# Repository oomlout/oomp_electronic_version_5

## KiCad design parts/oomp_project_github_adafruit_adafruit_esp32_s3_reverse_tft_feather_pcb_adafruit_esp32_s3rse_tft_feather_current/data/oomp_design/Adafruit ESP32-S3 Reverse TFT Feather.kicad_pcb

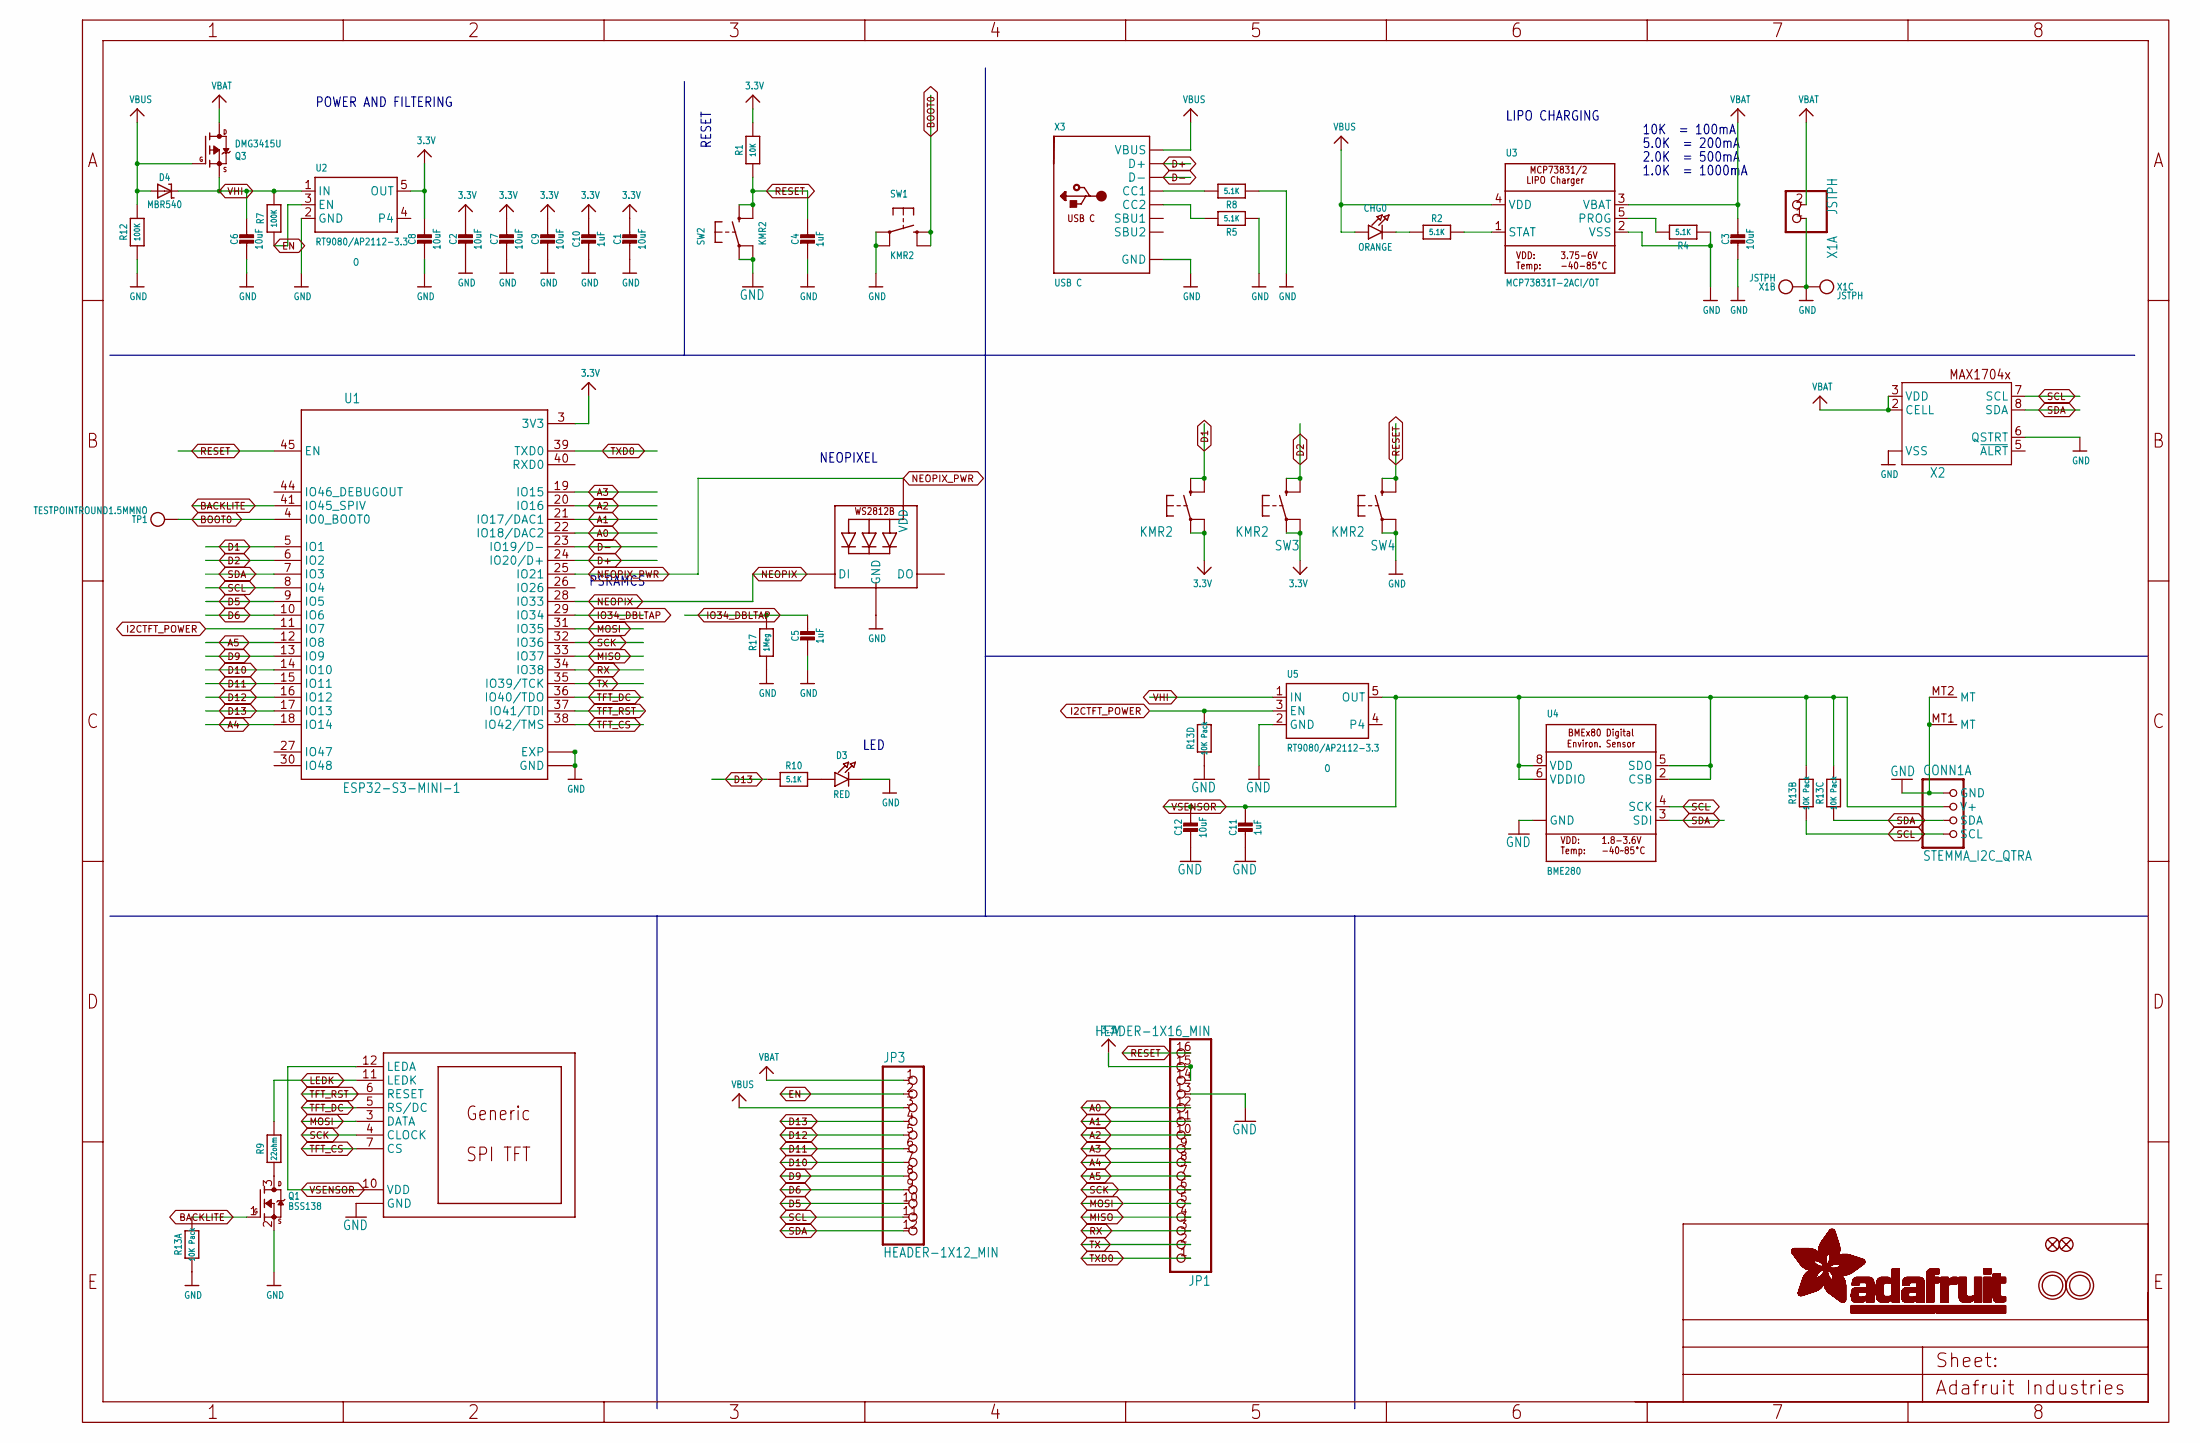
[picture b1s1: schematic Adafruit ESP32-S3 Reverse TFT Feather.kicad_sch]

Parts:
C1, C2, C3, C6, C7, C8, C9, C12: 10uF; 0805-NO
C4, C5, C10, C11: 1uF; 0603-NO
CHG0: ORANGE; CHIPLED_0603_NOOUTLINE
CONN1: STEMMA_I2C_QTRA; JST_SH4_RA; LCSC C145961
D3: RED; CHIPLED_0603_NOOUTLINE
D4: MBR540; SOD-123
DISP1: DISP_LCD_GENERIC_SPI_1.14IN_240X135_WRAPUNDER; TFT_1.14IN_240X135_WRAPUNDER
JP1: HEADER-1X16_MIN; 1X16_ROUND_MIN
JP3: HEADER-1X12_MIN; 1X12_ROUND_MIN
LED1: WS2812B_SK6805_1515; SK6805_1515; LCSC C2890035
Q1: BSS138; SC70
Q3: DMG3415U; SOT23-R
R1: 10K; 0603-NO
R2, R4, R5, R8, R10: 5.1K; 0603-NO
R7, R12: 100K; 0603-NO
R9: 22ohm; 0603-NO
R13: 10K Pack; RESPACK_4X0603
R17: 1Meg; 0603-NO
SW1, SW2, SW3, SW4, SW5: KMR2; BTN_RKB2_4.6X2.8
TP1: TESTPOINTROUND1.5MMNO; TESTPOINT_ROUND_1.5MM_NO
U1: ESP32-S3-MINI-1; ESP32-S2-MINI-1; MANUFACTURER_PART_NUMBER ESP32-S2-MINI-1
U2, U5: RT9080/AP2112-3.3; SOT23-5; JLC_ROTATION 0
U3: MCP73831T-2ACI/OT; SOT23-5; JLC_ROTATION 270
U4: BME280
U$31, U$32: MOUNTINGHOLE2.5; MOUNTINGHOLE_2.5_PLATED
U$34, U$35: FIDUCIAL_1MM
X1: JSTPH; JSTPH2_BATT; LCSC C47647
X2: MAX17048/T; TDFN8_2X2MM
X3: USB C; USB_C_CUSB31-CFM2AX-01-X; LCSC C165948

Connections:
3.3V: C1.1, C2.1, C7.1, C8.1, C9.1, C10.1, JP1.14, JP1.15, R1.2, SW3.A, SW3.A' (P1), SW5.A, SW5.A' (P1), U1.3 (3V3), U2.5 (OUT)
A0: JP1.12, U1.22 (IO18/DAC2)
A1: JP1.11, U1.21 (IO17/DAC1)
A2: JP1.10, U1.20 (IO16)
A3: JP1.9, U1.19 (IO15)
A4: JP1.8, U1.18 (IO14)
A5: JP1.7, U1.12 (IO8)
BACKLITE: Q1.1 (G), R13.8 (2), U1.41 (IO45_SPIV)
BOOT0: SW1.B (S), SW1.B' (S1), TP1.P$1, U1.4 (IO0_BOOT0)
D1: SW5.B (S), SW5.B' (S1), U1.5 (IO1)
D2: SW3.B (S), SW3.B' (S1), U1.6 (IO2)
D5: JP3.10, U1.9 (IO5)
D6: JP3.9, U1.10 (IO6)
D9: JP3.8, U1.13 (IO9)
D10: JP3.7, U1.14 (IO10)
D11: JP3.6, U1.15 (IO11)
D12: JP3.5, U1.16 (IO12)
D13: JP3.4, R10.1, U1.17 (IO13)
D+: U1.24 (IO20/D+), X3.A6 (D+), X3.B6 (D+)
D-: U1.23 (IO19/D-), X3.A7 (D-), X3.B7 (D-)
EN: JP3.2, R7.1, U2.3 (EN)
GND: C1.2, C2.2, C3.2, C4.2, C5.2, C6.2, C7.2, C8.2, C9.2, C10.2, C11.2, C12.2, CONN1.1 (GND), CONN1.MT1 (MT), CONN1.MT2 (MT), D3.C, DISP1.8 (GND), DISP1.13 (GND), JP1.13, LED1.4 (GND), Q1.2 (S), R4.1, R5.1, R8.1, R12.1, R13.1, R13.4 (1), R17.1, SW1.A, SW1.A' (P1), SW2.A, SW2.A' (P1), SW4.A, SW4.A' (P1), U1.1 (GND), U1.2 (GND), U1.42 (GND), U1.43 (GND), U1.46 (GND), U1.47 (GND), U1.48 (GND), U1.49 (GND), U1.50 (GND), U1.51 (GND), U1.52 (GND), U1.53 (GND), U1.54 (GND), U1.55 (GND), U1.56 (GND), U1.57 (GND), U1.58 (GND), U1.59 (GND), U1.60 (GND), U1.61 (EXP), U1.62 (GND), U1.63 (GND), U1.64 (GND), U1.65 (GND), U1.66 (EXP), U1.67 (EXP), U1.68 (EXP), U1.69 (EXP), U1.70 (EXP), U1.71 (EXP), U1.72 (EXP), U1.73 (EXP), U2.2 (GND), U3.2 (VSS), U4.1 (GND), U4.7 (GND), U5.2 (GND), X1.1, X1.NC1, X1.NC2, X2.1 (VSS), X2.4 (VSS), X2.6 (QSTRT), X2.THERMAL (VSS), X3.A1B12 (GND), X3.B1A12 (GND)
I2CTFT_POWER: R13.5 (2), U1.11 (IO7), U5.3 (EN)
IO34_DBLTAP: C5.1, R17.2, U1.29 (IO34)
LEDK: DISP1.11 (LEDK), R9.2
MISO: JP1.4, U1.33 (IO37)
MOSI: DISP1.3 (DATA), JP1.5, U1.31 (IO35)
unnamed: CHG0.C, R2.1
unnamed: Q1.3 (D), R9.1
unnamed: R2.2, U3.1 (STAT)
unnamed: R4.2, U3.5 (PROG)
unnamed: D3.A, R10.2
unnamed: R8.2, X3.A5 (CC1)
unnamed: R5.2, X3.B5 (CC2)
NEOPIX: LED1.1 (DI), U1.28 (IO33)
NEOPIX_PWR: LED1.2 (VDD), U1.25 (IO21)
RESET: C4.1, JP1.16, R1.1, SW2.B (S), SW2.B' (S1), SW4.B (S), SW4.B' (S1), U1.45 (EN)
RX: JP1.3, U1.34 (IO38)
SCK: DISP1.4 (CLOCK), JP1.6, U1.32 (IO36)
SCL: CONN1.4 (SCL), JP3.11, R13.2 (1), U1.8 (IO4), U4.4 (SCK), X2.7 (SCL)
SDA: CONN1.3 (SDA), JP3.12, R13.3 (1), U1.7 (IO3), U4.3 (SDI), X2.8 (SDA)
TFT_CS: DISP1.7 (CS), U1.38 (IO42/TMS)
TFT_DC: DISP1.5 (RS/DC), U1.36 (IO40/TDO)
TFT_RST: DISP1.6 (RESET), U1.37 (IO41/TDI)
TX: JP1.2, U1.35 (IO39/TCK)
TXD0: JP1.1, U1.39 (TXD0)
VBAT: C3.1, JP3.1, Q3.3 (D), U3.3 (VBAT), X1.2, X2.2 (CELL), X2.3 (VDD)
VBUS: CHG0.A, D4.A, JP3.3, Q3.1 (G), R12.2, U3.4 (VDD), X3.A4B9 (VBUS), X3.B4A9 (VBUS)
VHI: C6.1, D4.C, Q3.2 (S), R7.2, U2.1 (IN), U5.1 (IN)
VSENSOR: C11.1, C12.1, CONN1.2 (V+), DISP1.10 (VDD), DISP1.12 (LEDA), R13.6 (2), R13.7 (2), U4.2 (CSB), U4.5 (SDO), U4.6 (VDDIO), U4.8 (VDD), U5.5 (OUT)

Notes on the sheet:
LED
5.0K = 200mA
POWER AND FILTERING
10K = 100mA
LIPO CHARGING
NEOPIXEL
RESET
1.0K = 1000mA
PSRAMCS
2.0K = 500mA

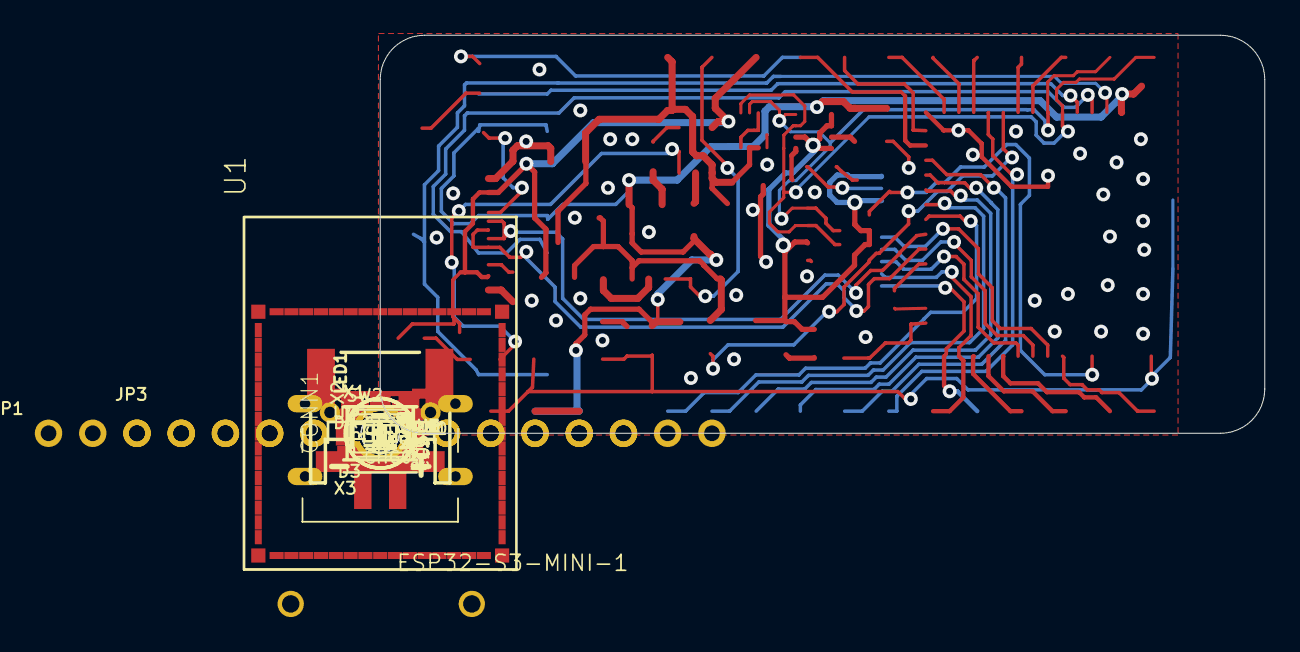
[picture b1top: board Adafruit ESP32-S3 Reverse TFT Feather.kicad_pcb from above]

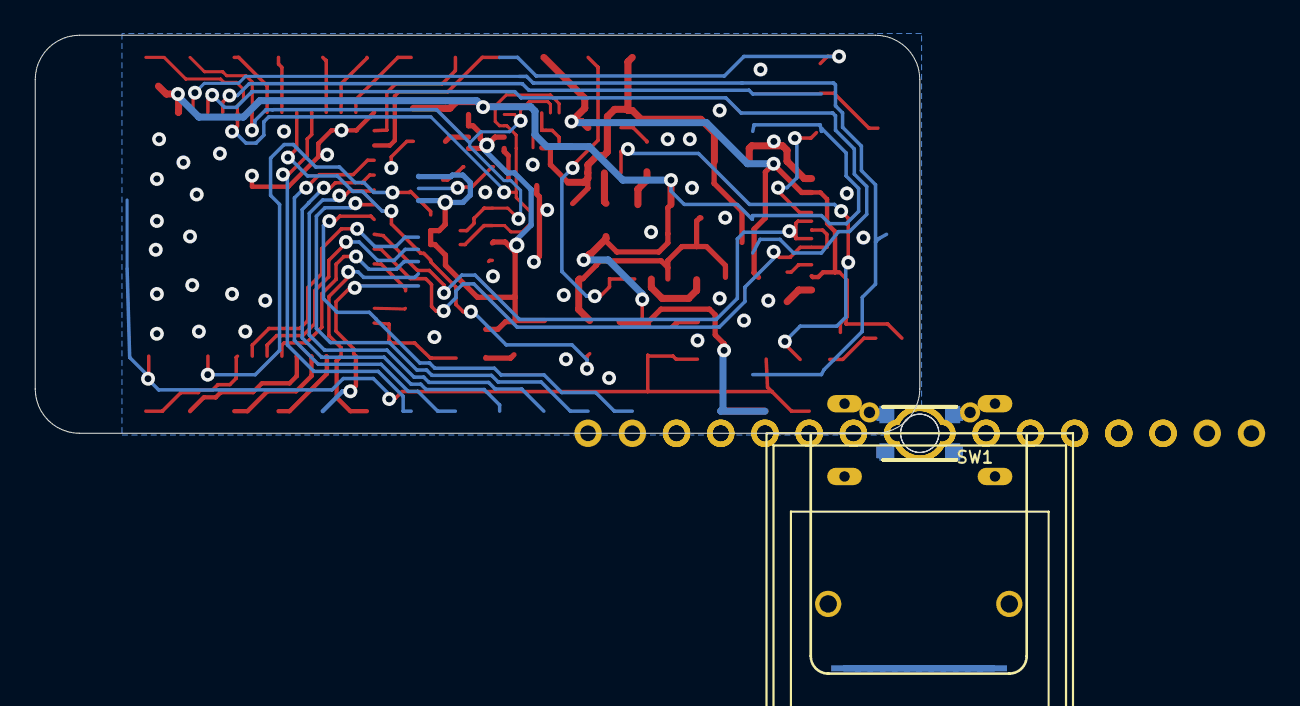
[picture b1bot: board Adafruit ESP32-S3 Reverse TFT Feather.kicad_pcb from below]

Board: 2 copper layers, 50.8 x 22.9 mm, 90 parts (11 on the bottom side), 50 nets.

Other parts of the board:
PLABEL0: PLABEL0
PLABEL1: PLABEL1
PLABEL2: PLABEL2
PLABEL3: PLABEL3
PLABEL4: PLABEL4
PLABEL5: PLABEL5
PLABEL6: PLABEL6
PLABEL7: PLABEL7
PLABEL8: PLABEL8
PLABEL9: PLABEL9
PLABEL10: PLABEL10
PLABEL11: PLABEL11
PLABEL12: PLABEL12
PLABEL13: PLABEL13
PLABEL14: PLABEL14
PLABEL15: PLABEL15
PLABEL16: PLABEL16
PLABEL17: PLABEL17
PLABEL18: PLABEL18
PLABEL19: PLABEL19
PLABEL20: PLABEL20
PLABEL21: PLABEL21
PLABEL22: PLABEL22
PLABEL23: PLABEL23
PLABEL24: PLABEL24
PLABEL25: PLABEL25
PLABEL26: PLABEL26
PLABEL27: PLABEL27
PLABEL28: PLABEL28
PLABEL29: PLABEL29
PLABEL30: PLABEL30
PLABEL31: PLABEL31
PLABEL33: PLABEL33
PLABEL34: PLABEL34
PLABEL35: PLABEL35
PLABEL36: PLABEL36
PLABEL37: PLABEL37
UNK_HOLE_0: dummyfp0
UNK_HOLE_1: dummyfp1

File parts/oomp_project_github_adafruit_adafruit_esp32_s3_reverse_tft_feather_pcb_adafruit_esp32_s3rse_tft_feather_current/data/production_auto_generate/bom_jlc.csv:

Comment,Designator,Footprint,LCSC Part #
,JP3,Adafruit ESP32-S3 Reverse TFT Feather-import-fps:1X12_ROUND_MIN,C7501588
,JP1,Adafruit ESP32-S3 Reverse TFT Feather-import-fps:1X16_ROUND_MIN,C7501270
,PLABEL0,Adafruit ESP32-S3 Reverse TFT Feather-import-fps:PLABEL0,
,PLABEL1,Adafruit ESP32-S3 Reverse TFT Feather-import-fps:PLABEL1,
,PLABEL10,Adafruit ESP32-S3 Reverse TFT Feather-import-fps:PLABEL10,
,PLABEL11,Adafruit ESP32-S3 Reverse TFT Feather-import-fps:PLABEL11,
,PLABEL12,Adafruit ESP32-S3 Reverse TFT Feather-import-fps:PLABEL12,
,PLABEL13,Adafruit ESP32-S3 Reverse TFT Feather-import-fps:PLABEL13,
,PLABEL14,Adafruit ESP32-S3 Reverse TFT Feather-import-fps:PLABEL14,
,PLABEL15,Adafruit ESP32-S3 Reverse TFT Feather-import-fps:PLABEL15,
,PLABEL16,Adafruit ESP32-S3 Reverse TFT Feather-import-fps:PLABEL16,
,PLABEL17,Adafruit ESP32-S3 Reverse TFT Feather-import-fps:PLABEL17,
,PLABEL18,Adafruit ESP32-S3 Reverse TFT Feather-import-fps:PLABEL18,
,PLABEL19,Adafruit ESP32-S3 Reverse TFT Feather-import-fps:PLABEL19,
,PLABEL2,Adafruit ESP32-S3 Reverse TFT Feather-import-fps:PLABEL2,
,PLABEL20,Adafruit ESP32-S3 Reverse TFT Feather-import-fps:PLABEL20,
,PLABEL21,Adafruit ESP32-S3 Reverse TFT Feather-import-fps:PLABEL21,
,PLABEL22,Adafruit ESP32-S3 Reverse TFT Feather-import-fps:PLABEL22,
,PLABEL23,Adafruit ESP32-S3 Reverse TFT Feather-import-fps:PLABEL23,
,PLABEL24,Adafruit ESP32-S3 Reverse TFT Feather-import-fps:PLABEL24,
,PLABEL25,Adafruit ESP32-S3 Reverse TFT Feather-import-fps:PLABEL25,
,PLABEL26,Adafruit ESP32-S3 Reverse TFT Feather-import-fps:PLABEL26,
,PLABEL27,Adafruit ESP32-S3 Reverse TFT Feather-import-fps:PLABEL27,
,PLABEL28,Adafruit ESP32-S3 Reverse TFT Feather-import-fps:PLABEL28,
,PLABEL29,Adafruit ESP32-S3 Reverse TFT Feather-import-fps:PLABEL29,
,PLABEL3,Adafruit ESP32-S3 Reverse TFT Feather-import-fps:PLABEL3,
,PLABEL30,Adafruit ESP32-S3 Reverse TFT Feather-import-fps:PLABEL30,
,PLABEL31,Adafruit ESP32-S3 Reverse TFT Feather-import-fps:PLABEL31,
,PLABEL33,Adafruit ESP32-S3 Reverse TFT Feather-import-fps:PLABEL33,
,PLABEL34,Adafruit ESP32-S3 Reverse TFT Feather-import-fps:PLABEL34,
,PLABEL35,Adafruit ESP32-S3 Reverse TFT Feather-import-fps:PLABEL35,
,PLABEL36,Adafruit ESP32-S3 Reverse TFT Feather-import-fps:PLABEL36,
,PLABEL37,Adafruit ESP32-S3 Reverse TFT Feather-import-fps:PLABEL37,
,PLABEL4,Adafruit ESP32-S3 Reverse TFT Feather-import-fps:PLABEL4,
,PLABEL5,Adafruit ESP32-S3 Reverse TFT Feather-import-fps:PLABEL5,
,PLABEL6,Adafruit ESP32-S3 Reverse TFT Feather-import-fps:PLABEL6,
,PLABEL7,Adafruit ESP32-S3 Reverse TFT Feather-import-fps:PLABEL7,
,PLABEL8,Adafruit ESP32-S3 Reverse TFT Feather-import-fps:PLABEL8,
,PLABEL9,Adafruit ESP32-S3 Reverse TFT Feather-import-fps:PLABEL9,
,TP1,Adafruit ESP32-S3 Reverse TFT Feather-import-fps:TESTPOINT_ROUND_1.5MM_NO,
100K,"R7,R12",Adafruit ESP32-S3 Reverse TFT Feather-import-fps:0603-NO,C25803
10K,R1,Adafruit ESP32-S3 Reverse TFT Feather-import-fps:0603-NO,C98220
10K Pack,R13,Adafruit ESP32-S3 Reverse TFT Feather-import-fps:RESPACK_4X0603,C98220
10uF,"C1,C2,C3,C6,C7,C8,C9,C12",Adafruit ESP32-S3 Reverse TFT Feather-import-fps:0805-NO,
1Meg,R17,Adafruit ESP32-S3 Reverse TFT Feather-import-fps:0603-NO,C2907003
1uF,"C4,C5,C10,C11",Adafruit ESP32-S3 Reverse TFT Feather-import-fps:0603-NO,C5673
22ohm,R9,Adafruit ESP32-S3 Reverse TFT Feather-import-fps:0603-NO,C23345
5.1K,"R2,R4,R5,R8,R10",Adafruit ESP32-S3 Reverse TFT Feather-import-fps:0603-NO,C23186
BME280,U4,Adafruit ESP32-S3 Reverse TFT Feather-import-fps:BME280,
BSS138,Q1,Adafruit ESP32-S3 Reverse TFT Feather-import-fps:SC70,C52895
DISP_LCD_GENERIC_SPI_1.14IN_240X135_WRAPUNDER,DISP1,Adafruit ESP32-S3 Reverse TFT Feather-import-fps:TFT_1.14IN_240X135_WRAPUNDER,
DMG3415U,Q3,Adafruit ESP32-S3 Reverse TFT Feather-import-fps:SOT23-R,
ESP32-S3-MINI-1,U1,Adafruit ESP32-S3 Reverse TFT Feather-import-fps:ESP32-S2-MINI-1,
FIDUCIAL_1MM,"U$34,U$35",Adafruit ESP32-S3 Reverse TFT Feather-import-fps:FIDUCIAL_1MM,
JSTPH,X1,Adafruit ESP32-S3 Reverse TFT Feather-import-fps:JSTPH2_BATT,
KMR2,"SW1,SW2,SW3,SW4,SW5",Adafruit ESP32-S3 Reverse TFT Feather-import-fps:BTN_RKB2_4.6X2.8,
MAX17048/T,X2,Adafruit ESP32-S3 Reverse TFT Feather-import-fps:TDFN8_2X2MM,
MBR540,D4,Adafruit ESP32-S3 Reverse TFT Feather-import-fps:SOD-123,
MCP73831T-2ACI/OT,U3,Adafruit ESP32-S3 Reverse TFT Feather-import-fps:SOT23-5,
ORANGE,CHG0,Adafruit ESP32-S3 Reverse TFT Feather-import-fps:CHIPLED_0603_NOOUTLINE,
RED,D3,Adafruit ESP32-S3 Reverse TFT Feather-import-fps:CHIPLED_0603_NOOUTLINE,
RT9080/AP2112-3.3,"U2,U5",Adafruit ESP32-S3 Reverse TFT Feather-import-fps:SOT23-5,
STEMMA_I2C_QTRA,CONN1,Adafruit ESP32-S3 Reverse TFT Feather-import-fps:JST_SH4_RA,
USB C,X3,Adafruit ESP32-S3 Reverse TFT Feather-import-fps:USB_C_CUSB31-CFM2AX-01-X,
WS2812B_SK6805_1515,LED1,Adafruit ESP32-S3 Reverse TFT Feather-import-fps:SK6805_1515,

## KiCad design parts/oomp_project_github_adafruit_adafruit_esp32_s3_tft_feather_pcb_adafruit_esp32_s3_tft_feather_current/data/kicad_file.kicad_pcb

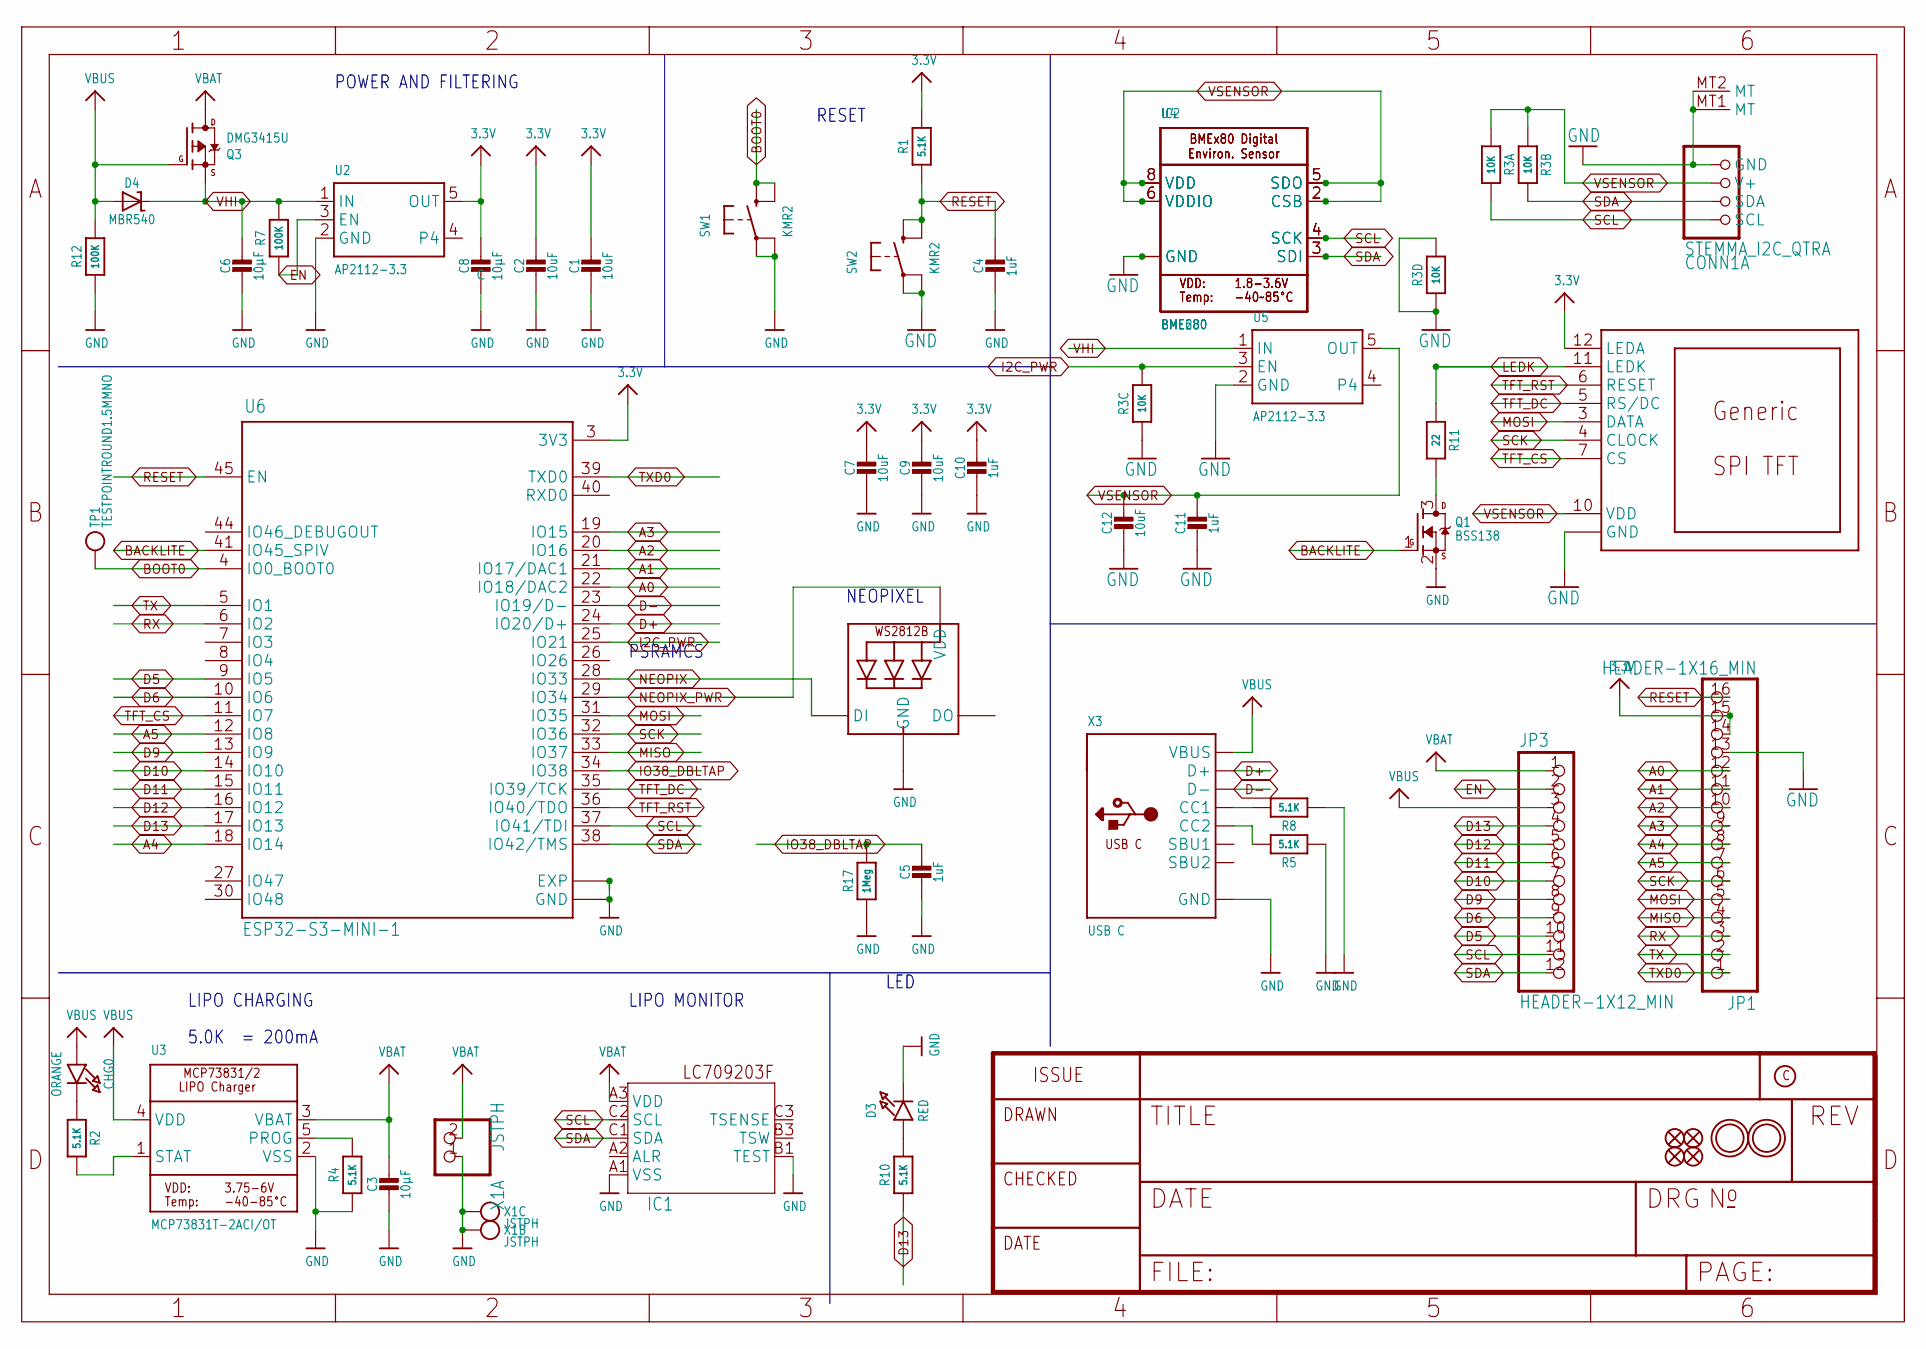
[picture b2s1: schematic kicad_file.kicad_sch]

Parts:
C1, C2, C7, C9, C12: 10uF; 0805-NO
C3, C6, C8: 10µF; 0805-NO
C4, C5, C10, C11: 1uF; 0603-NO
CHG0: ORANGE; CHIPLED_0603_NOOUTLINE
CONN1: STEMMA_I2C_QTRA; JST_SH4_RA
D3: RED; CHIPLED_0603_NOOUTLINE
D4: MBR540; SOD-123
DISP1: DISP_LCD_GENERIC_SPI_1.14IN_240X135_WRAPUNDER; TFT_1.14IN_240X135_WRAPUNDER
IC1: LC709203F/MH; WLCSP9
IC2: BME680
JP1: HEADER-1X16_MIN; 1X16_ROUND_MIN
JP3: HEADER-1X12_MIN; 1X12_ROUND_MIN
LED1: WS2812B_SK6805_1515; SK6805_1515
Q1: BSS138; SOT23-R
Q3: DMG3415U; SOT23-R
R1, R2, R4, R5, R8, R10: 5.1K; 0603-NO
R3: 10K; RESPACK_4X0603
R7, R12: 100K; 0603-NO
R11: 22; 0603-NO
R17: 1Meg; 0603-NO
SW1, SW2: KMR2; BTN_KMR2_4.6X2.8
TP1: TESTPOINTROUND1.5MMNO; TESTPOINT_ROUND_1.5MM_NO
U2, U5: AP2112-3.3; SOT23-5
U3: MCP73831T-2ACI/OT; SOT23-5
U4: BME280
U6: ESP32-S3-MINI-1; QFN60_ESP32-S2-MINI-1_EXP; MANUFACTURER_PART_NUMBER ESP32-S2-MINI-1
U$31, U$32: MOUNTINGHOLE2.5; MOUNTINGHOLE_2.5_PLATED
U$34, U$35, U$55, U$56: FIDUCIAL_1MM
X1: JSTPH; JSTPH2_BATT
X3: USB C; USB_C_CUSB31-CFM2AX-01-X

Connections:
3.3V: C1.1, C2.1, C7.1, C8.1, C9.1, C10.1, DISP1.12 (LEDA), JP1.14, JP1.15, R1.2, U2.5 (OUT), U6.3 (3V3)
A0: JP1.12, U6.22 (IO18/DAC2)
A1: JP1.11, U6.21 (IO17/DAC1)
A2: JP1.10, U6.20 (IO16)
A3: JP1.9, U6.19 (IO15)
A4: JP1.8, U6.18 (IO14)
A5: JP1.7, U6.12 (IO8)
BACKLITE: Q1.1 (G), U6.41 (IO45_SPIV)
BOOT0: SW1.B (S), SW1.B' (S1), TP1.P$1, U6.4 (IO0_BOOT0)
D5: JP3.10, U6.9 (IO5)
D6: JP3.9, U6.10 (IO6)
D9: JP3.8, U6.13 (IO9)
D10: JP3.7, U6.14 (IO10)
D11: JP3.6, U6.15 (IO11)
D12: JP3.5, U6.16 (IO12)
D13: JP3.4, R10.1, U6.17 (IO13)
D+: U6.24 (IO20/D+), X3.A6 (D+), X3.B6 (D+)
D-: U6.23 (IO19/D-), X3.A7 (D-), X3.B7 (D-)
EN: JP3.2, R7.1, U2.3 (EN)
GND: C1.2, C2.2, C3.2, C4.2, C5.2, C6.2, C7.2, C8.2, C9.2, C10.2, C11.2, C12.2, CONN1.1 (GND), CONN1.MT1 (MT), CONN1.MT2 (MT), D3.C, DISP1.8 (GND), DISP1.13 (GND), IC1.A1 (VSS), IC1.B1 (TEST), IC2.1 (GND), IC2.7 (GND), JP1.13, LED1.4 (GND), Q1.2 (S), R3.3 (1), R3.4 (1), R3.5 (2), R4.1, R5.1, R8.1, R12.1, R17.1, SW1.A, SW1.A' (P1), SW2.A, SW2.A' (P1), U2.2 (GND), U3.2 (VSS), U4.1 (GND), U4.7 (GND), U5.2 (GND), U6.1 (GND), U6.2 (GND), U6.42 (GND), U6.43 (GND), U6.46 (GND), U6.47 (GND), U6.48 (GND), U6.49 (GND), U6.50 (GND), U6.51 (GND), U6.52 (GND), U6.53 (GND), U6.54 (GND), U6.55 (GND), U6.56 (GND), U6.57 (GND), U6.58 (GND), U6.59 (GND), U6.60 (GND), U6.61 (EXP), U6.62 (GND), U6.63 (GND), U6.64 (GND), U6.65 (GND), U6.66 (EXP), U6.67 (EXP), U6.68 (EXP), U6.69 (EXP), U6.70 (EXP), U6.71 (EXP), U6.72 (EXP), U6.73 (EXP), X1.1, X1.NC1, X1.NC2, X3.A1B12 (GND), X3.B1A12 (GND)
I2C_PWR: R3.6 (2), U5.3 (EN), U6.25 (IO21)
IO38_DBLTAP: C5.1, R17.2, U6.34 (IO38)
LEDK: DISP1.11 (LEDK), R11.1
MISO: JP1.4, U6.33 (IO37)
MOSI: DISP1.3 (DATA), JP1.5, U6.31 (IO35)
unnamed: CHG0.C, R2.1
unnamed: Q1.3 (D), R11.2
unnamed: R2.2, U3.1 (STAT)
unnamed: R4.2, U3.5 (PROG)
unnamed: D3.A, R10.2
unnamed: R8.2, X3.A5 (CC1)
unnamed: R5.2, X3.B5 (CC2)
NEOPIX: LED1.1 (DI), U6.28 (IO33)
NEOPIX_PWR: LED1.2 (VDD), U6.29 (IO34)
RESET: C4.1, JP1.16, R1.1, SW2.B (S), SW2.B' (S1), U6.45 (EN)
RX: JP1.3, U6.6 (IO2)
SCK: DISP1.4 (CLOCK), JP1.6, U6.32 (IO36)
SCL: CONN1.4 (SCL), IC1.C2 (SCL), IC2.4 (SCK), JP3.11, R3.8 (2), U4.4 (SCK), U6.37 (IO41/TDI)
SDA: CONN1.3 (SDA), IC1.C1 (SDA), IC2.3 (SDI), JP3.12, R3.7 (2), U4.3 (SDI), U6.38 (IO42/TMS)
TFT_CS: DISP1.7 (CS), U6.11 (IO7)
TFT_DC: DISP1.5 (RS/DC), U6.35 (IO39/TCK)
TFT_RST: DISP1.6 (RESET), U6.36 (IO40/TDO)
TX: JP1.2, U6.5 (IO1)
TXD0: JP1.1, U6.39 (TXD0)
VBAT: C3.1, IC1.A3 (VDD), JP3.1, Q3.3 (D), U3.3 (VBAT), X1.2
VBUS: CHG0.A, D4.A, JP3.3, Q3.1 (G), R12.2, U3.4 (VDD), X3.A4B9 (VBUS), X3.B4A9 (VBUS)
VHI: C6.1, D4.C, Q3.2 (S), R7.2, U2.1 (IN), U5.1 (IN)
VSENSOR: C11.1, C12.1, CONN1.2 (V+), DISP1.10 (VDD), IC2.2 (CSB), IC2.5 (SDO), IC2.6 (VDDIO), IC2.8 (VDD), R3.1, R3.2 (1), U4.2 (CSB), U4.5 (SDO), U4.6 (VDDIO), U4.8 (VDD), U5.5 (OUT)

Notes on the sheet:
LED
RESET
5.0K = 200mA
NEOPIXEL
LIPO MONITOR
POWER AND FILTERING
PSRAMCS
LIPO CHARGING

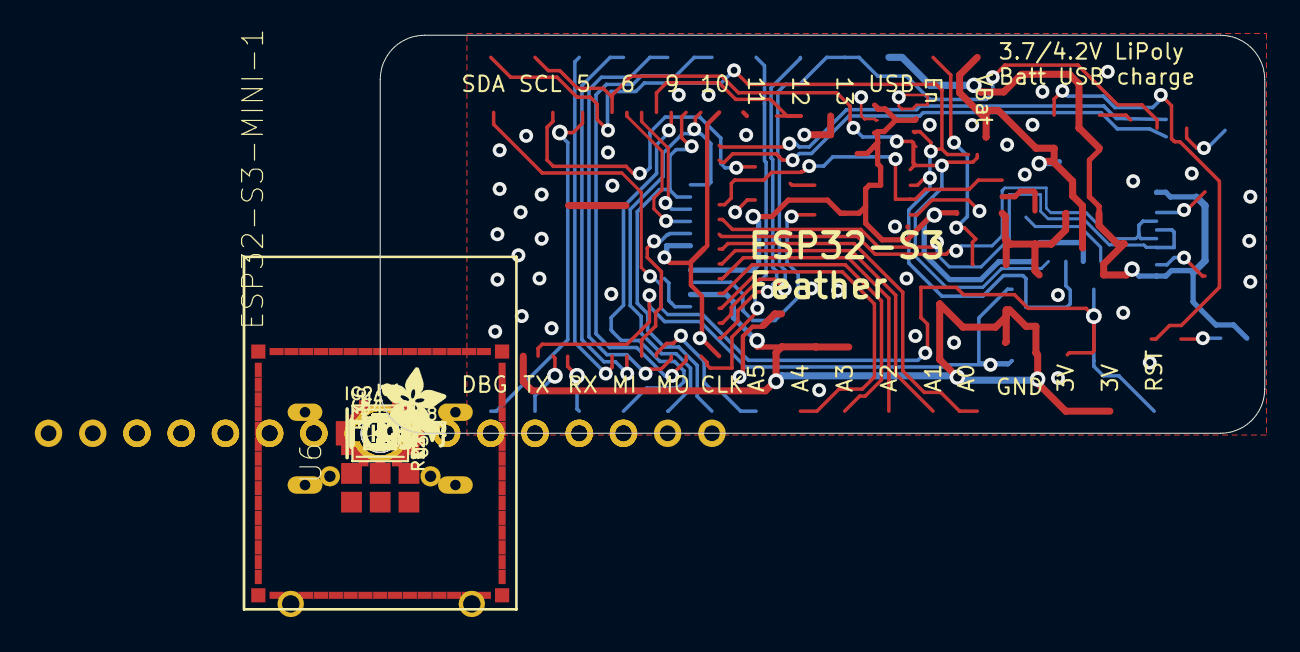
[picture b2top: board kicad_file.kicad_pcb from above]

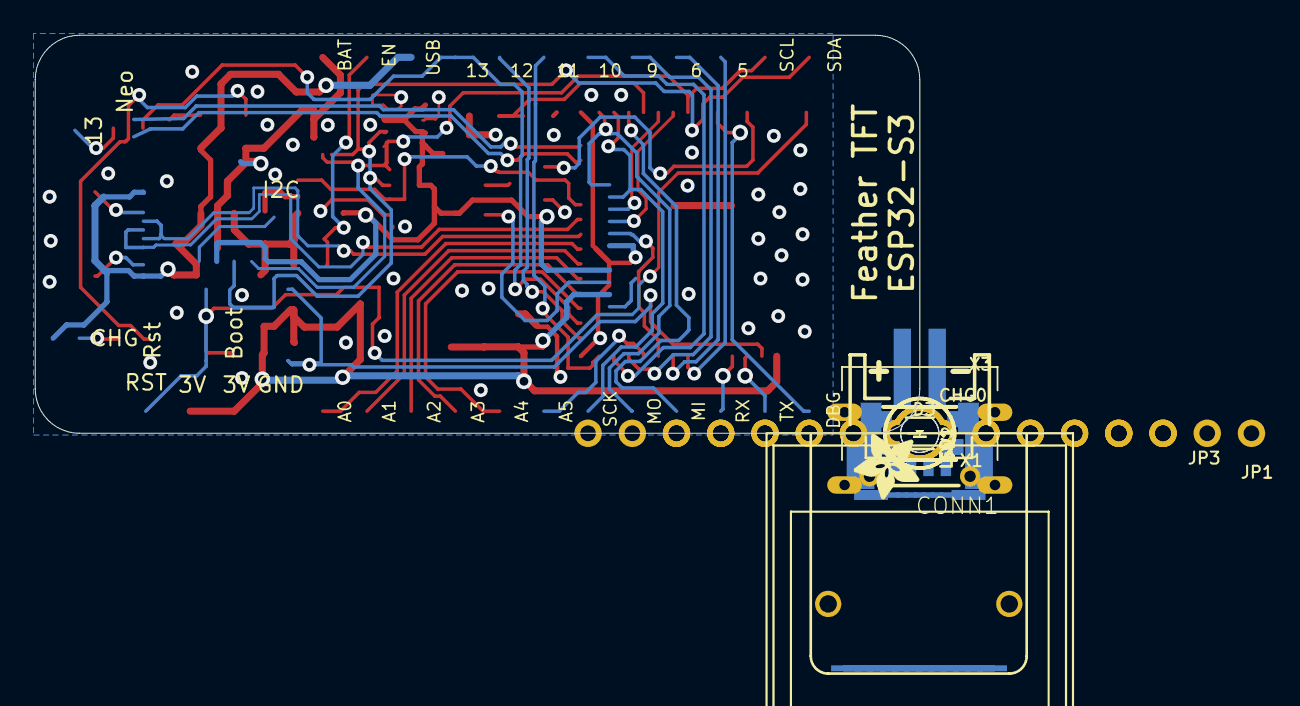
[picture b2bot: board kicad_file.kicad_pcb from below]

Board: 2 copper layers, 50.8 x 22.9 mm, 56 parts (16 on the bottom side), 48 nets.

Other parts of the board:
U$7: PCBFEAT-REV-040
U$9, U$54: ADAFRUIT_3.5MM
UNK_HOLE_0: dummyfp0
UNK_HOLE_1: dummyfp1

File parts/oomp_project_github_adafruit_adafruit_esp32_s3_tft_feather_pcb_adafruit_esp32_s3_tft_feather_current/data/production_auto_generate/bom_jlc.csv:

Comment,Designator,Footprint,LCSC Part #
,JP3,Adafruit ESP32-S3 TFT Feather-import-fps:1X12_ROUND_MIN,C7501588
,JP1,Adafruit ESP32-S3 TFT Feather-import-fps:1X16_ROUND_MIN,C7501270
,"U$9,U$54",Adafruit ESP32-S3 TFT Feather-import-fps:ADAFRUIT_3.5MM,
,U$7,Adafruit ESP32-S3 TFT Feather-import-fps:PCBFEAT-REV-040,
,TP1,Adafruit ESP32-S3 TFT Feather-import-fps:TESTPOINT_ROUND_1.5MM_NO,
100K,"R7,R12",Adafruit ESP32-S3 TFT Feather-import-fps:0603-NO,C25803
10K,R3,Adafruit ESP32-S3 TFT Feather-import-fps:RESPACK_4X0603,C98220
10uF,"C1,C2,C7,C9,C12",Adafruit ESP32-S3 TFT Feather-import-fps:0805-NO,
10µF,"C3,C6,C8",Adafruit ESP32-S3 TFT Feather-import-fps:0805-NO,
1Meg,R17,Adafruit ESP32-S3 TFT Feather-import-fps:0603-NO,C2907003
1uF,"C4,C5,C10,C11",Adafruit ESP32-S3 TFT Feather-import-fps:0603-NO,C5673
22,R11,Adafruit ESP32-S3 TFT Feather-import-fps:0603-NO,C23345
5.1K,"R1,R2,R4,R5,R8,R10",Adafruit ESP32-S3 TFT Feather-import-fps:0603-NO,C23186
AP2112-3.3,"U2,U5",Adafruit ESP32-S3 TFT Feather-import-fps:SOT23-5,
BME280,U4,Adafruit ESP32-S3 TFT Feather-import-fps:BME280,
BME680,IC2,Adafruit ESP32-S3 TFT Feather-import-fps:BME680,
BSS138,Q1,Adafruit ESP32-S3 TFT Feather-import-fps:SOT23-R,C52895
DISP_LCD_GENERIC_SPI_1.14IN_240X135_WRAPUNDER,DISP1,Adafruit ESP32-S3 TFT Feather-import-fps:TFT_1.14IN_240X135_WRAPUNDER,
DMG3415U,Q3,Adafruit ESP32-S3 TFT Feather-import-fps:SOT23-R,
ESP32-S3-MINI-1,U6,Adafruit ESP32-S3 TFT Feather-import-fps:QFN60_ESP32-S2-MINI-1_EXP,
FIDUCIAL_1MM,"U$34,U$35,U$55,U$56",Adafruit ESP32-S3 TFT Feather-import-fps:FIDUCIAL_1MM,
JSTPH,X1,Adafruit ESP32-S3 TFT Feather-import-fps:JSTPH2_BATT,
KMR2,"SW1,SW2",Adafruit ESP32-S3 TFT Feather-import-fps:BTN_KMR2_4.6X2.8,
LC709203F/MH,IC1,Adafruit ESP32-S3 TFT Feather-import-fps:WLCSP9,
MBR540,D4,Adafruit ESP32-S3 TFT Feather-import-fps:SOD-123,
MCP73831T-2ACI/OT,U3,Adafruit ESP32-S3 TFT Feather-import-fps:SOT23-5,
ORANGE,CHG0,Adafruit ESP32-S3 TFT Feather-import-fps:CHIPLED_0603_NOOUTLINE,
RED,D3,Adafruit ESP32-S3 TFT Feather-import-fps:CHIPLED_0603_NOOUTLINE,
STEMMA_I2C_QTRA,CONN1,Adafruit ESP32-S3 TFT Feather-import-fps:JST_SH4_RA,
USB C,X3,Adafruit ESP32-S3 TFT Feather-import-fps:USB_C_CUSB31-CFM2AX-01-X,
WS2812B_SK6805_1515,LED1,Adafruit ESP32-S3 TFT Feather-import-fps:SK6805_1515,

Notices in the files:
parts and their libraries:
COPYRIGHT: Copyright (C) 2018 Accelerated Designs. All rights reserved
